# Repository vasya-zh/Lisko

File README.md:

# Lisko

## Overview

Lisko is a EFM32PG23 devboard - micro version of the [Gecko PG23](https://www.silabs.com/development-tools/mcu/32-bit/efm32pg23-pro-kit?tab=overview) development board with NUCLEO-G431KB/Arduino-Nano-v3 pinout.

Lisko is breadboard and custom PCB ready, you can easily check your concept designs with EFM32 MCU

## Features

- EFM32PG23B200F512IM40 MCU with 512kB Flash, 64kB RAM, Secure Vault and almost all reroutable GPIOs
- onboard SWD Flasher based on STM32 with edge USB-C connector
- 32Mbit external Flash chip W25Q32JVSNIQ
- 64Mbit external PSRAM chip APS6404L-SQN-SN
- 24PIN E-INK connector with driver schematics, connected to EFM32PF23 MCU
- External MCU 1.7-3.8V power input for enegry-efficient devices 
- Build in 3.3V LDO with 150mA output pin to power the board from USB or external source VIN pin
- User LED on PA003 pin
- Reset button
- many LEDs for debugging - Power OK, flashing error, Flasher activity
- 30pin Arduino-Nano-v3/NUCLEO-G431KB pinout
- KiCad footprint to use it in your PCBs
- full OSHW, made with KiCad - the best ECAD

## Why did you create this?

We want to help people tinker with beautiful EFM32PG23 microcontroller more cheaply and handily.

## Why EFM32PG23?

This SiLabs MCU has many handy features, we use it mostly because of its Secure Vault and low power consumption for small security devices like crypto wallets or e-locks.

All the chip specs and datasheets can be found on the [EFM32PG23 MCU page](https://www.silabs.com/mcu/32-bit-microcontrollers/efm32pg23-series-2)

## Why do you call it Lisko?

The original SiLabs EFM32 microcontroller line is called Gecko, Lisko is a Finnish word for Gecko, thats simple. 

## How to make Lisko on your own

You can produce Lisko PCBs on any PCB fab you work with, for example, JLCPCB, PCBWAY or OSHPARK, the output files are ready for these fabs.

Gerber files are available in [/production](production/) folder

PCB Specs for order:
- Layers: 4
- Board thickness: 0.8mm - if you make it a different thickness it will not fit inside the USB-C connector
- Surface treatment: ENIG - it's important, don't use HASL or any other surface, it will add thickness and destroy your USB-C cable
- PCB colour/mask: green
- Silkscreen colour: white

You can order PCBs with assembly at your Fab, the [files](production/) are production ready and machine-readable and tested with JLCPCB.

Or order the [parts](docs/) separately and assemble the board on your own.

CSV BOM and interactive HTML BOM are available in [/docs](docs/) folder

All the parts are available at Mouser, Digikey and LCSC (and JLCPCB PCB assembly with LCSC warehouse too)

- [Digikey shared basket](https://www.digikey.fi/short/m47mv8nd)
- [Mouser shared basket](https://www.mouser.fi/ProjectManager/ProjectDetail.aspx?AccessID=fcf13b51e8)

We tried to make BOM as small as possible for this amount of features.

## How to flash your Lisko board

First of all, you need to upload the flasher firmware:

0. Install STM32 DFU flashing software for example [stm32cubeprog](https://www.st.com/en/development-tools/stm32cubeprog.html)
	
	Or install alternative DFU software, for example dfu-util tool:
	
	On a Linux machine you can install it using:

	```
	sudo apt-get install dfu-util
	```
	
	for other systems, see http://dfu-util.sourceforge.net/

1. Hold RESET button and connect Lisko to your PC with a USB-C cable

2. STM32 flasher MCU will go to DFU mode and appear in your system as a DFU device. You can check its availability using:

	```
	dfu-util --list
	```
	You should see something like this:
	```
	dfu-util --list
	dfu-util 0.8

	Copyright 2005-2009 Weston Schmidt, Harald Welte and OpenMoko Inc.
	Copyright 2010-2014 Tormod Volden and Stefan Schmidt
	This program is Free Software and has ABSOLUTELY NO WARRANTY
	Please report bugs to dfu-util@lists.gnumonks.org

	Found DFU: [0483:df11] ver=2200, devnum=49, cfg=1, intf=0, alt=3, name="@Device Feature/0xFFFF0000/01*004 e", serial="315A35663432"
	```

3. Now you can flash the flasher by using:

	```
	dfu-util -a 0 --dfuse-address 0x08000000 -D pilkki_0.0.1.bin
	```

	from the folder, there pilkki_0.0.1.bin file was placed. By default, you can find it in [/flasher-firmware](flasher-firmware/) folder of this repository.

4. Perfect!

If you want to tinker with the flasher firmware, you can find the source code in [Pilkki repo](https://github.com/Kalapaja/pilkki/tree/main/firmware)

## How to program your Lisko board

Binary firmware can be uploaded to Lisko EFM32 MCU using [Pilkki software](https://github.com/Kalapaja/pilkki/tree/main/software)

You can find test projects here:

- In C - in folder [/test-firmware](test-firmware/)

- Or in Rust - [Kampela project](https://github.com/Kalapaja/kampela-firmware)

## How to use Lisko in your PCB project

You can use Lisko with your breadboard prototype, see the pinout diagram and schematics for details.

Or you can integrate Lisko in your PCB as a module with SMD soldering or soldering it with two 15-pin 2.54mm pitch headers.

You can find the KiCad library and 3d models in [/kicad-library](kicad-library/) folder.

An example of module usage can be found in [Kampela Soldering Kit](https://github.com/vasya-zh/kampela-soldering-kit) project.

## About the PCB:

Lisko A1 is made on a 4-layers 0.8mm PCB. 

4 layers make the layout clean and easy and can be produced at any factory with no problem.

Designs and documentation are available in:
- [/kicad](kicad/) - [KiCad](https://www.kicad.org/) design files
- [/docs](docs/) - PDF schematics, interactive HTML BOM, pinout spreadsheet and CSV BOM

0.8mm is used because of the edge USB-C connector used in Lisko to make it cheaper and easier to reproduce. If you can make a device with fewer components, why not do it? Edge USB-C connector inserts directly in a common USB-C cable and works as a USB 2.0 device.

USB Edge connector KiCad library available at [PCB Edge USB connector library](https://github.com/vasya-zh/PCB-Edge-USB-connector-KiCad-library)

## TODO
- Add flasher firmware source code to this repo
- Improve flasher software docs for all OS's and add builds/releases
- Add SWD debugger functions in firmware and Pilkki software/OpenOCD support
- Add the project to https://kitspace.org/

## Contributors

- [Vasilii Zhuravskii](https://github.com/vasya-zh) - Lisko devboard idea, schematics, board design, DFM, docs, tests

- [Yuri Ilin](https://www.youtube.com/@katsuk) - schematics source (Pilkki and Kampela), flasher firmware, EFM32 test firmware in C with E-INK and other features

This project was made at [Alzymologist Oy](https://github.com/alzymologist) as a part of [Kampela](https://kampe.la) project.

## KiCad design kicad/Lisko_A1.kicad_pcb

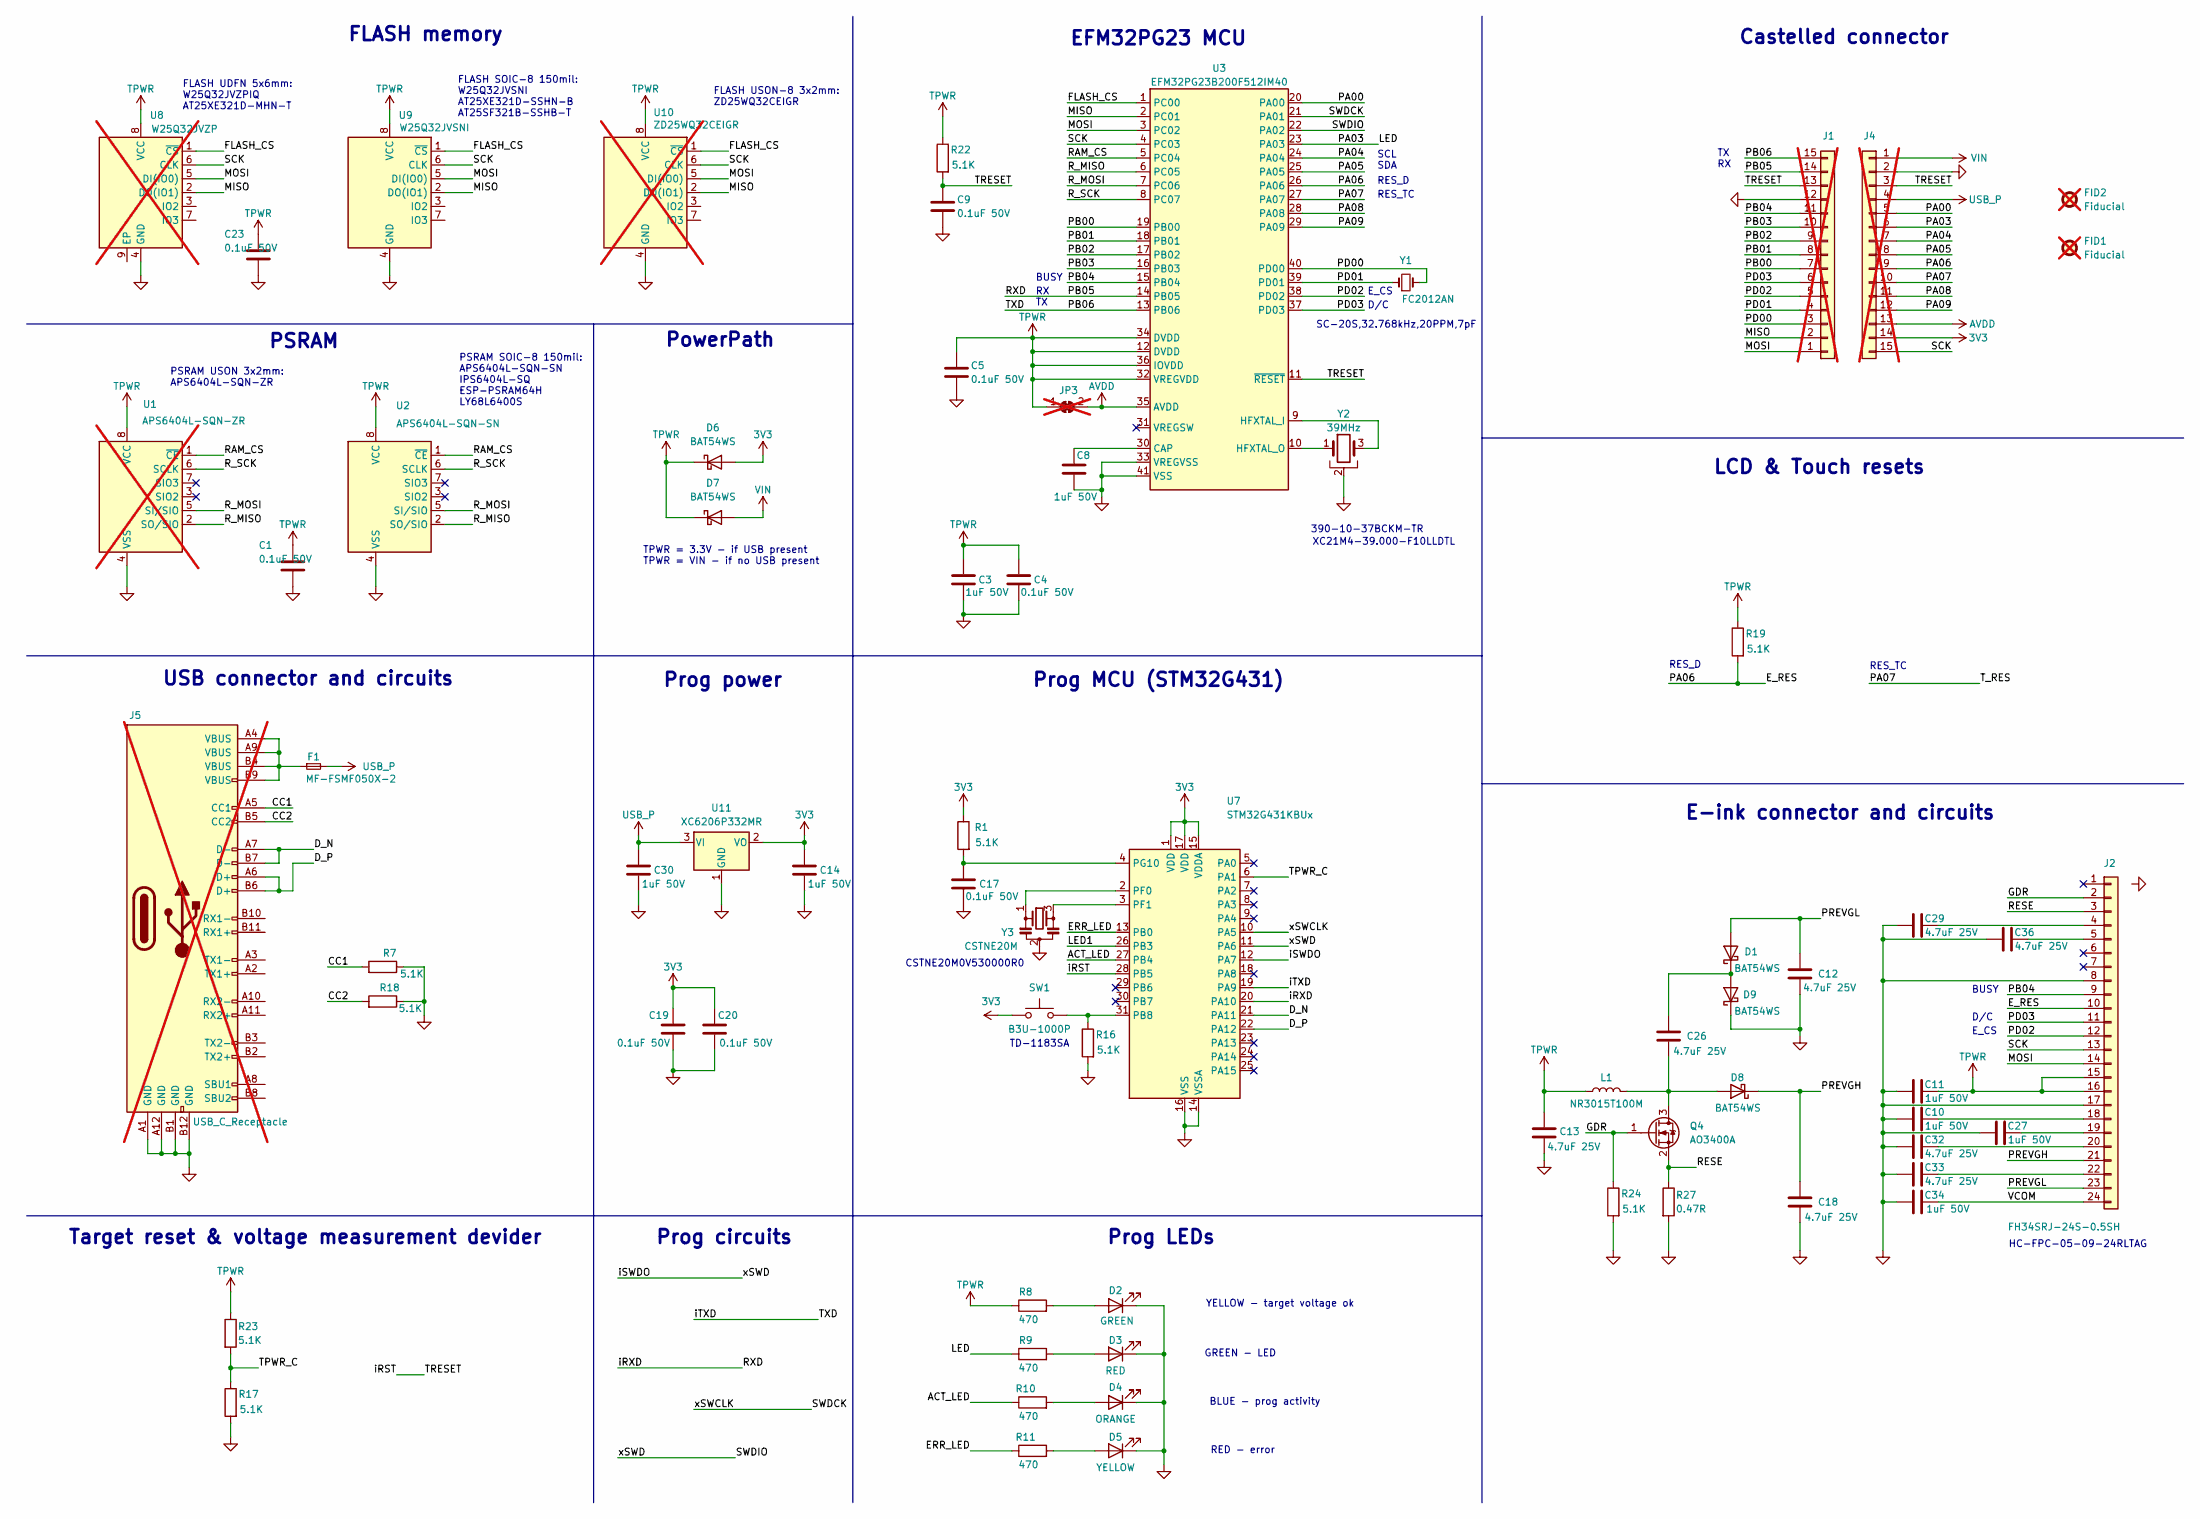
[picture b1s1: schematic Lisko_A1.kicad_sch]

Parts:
C1, C4, C5, C9, C17, C19, C20, C23: 0.1uF 50V; C_0402_1005Metric; Mouser Part # 187-CL05B104KB5NNWC; LCSC Part # C5142567
C3, C8, C10, C11, C14, C27, C30, C34: 1uF 50V; C_0402_1005Metric; Mouser Part # 81-GRM155R61H105KE5J; LCSC Part # C1518208
C12, C13, C18, C26, C29, C32, C33, C36: 4.7uF 25V; C_0603_1608Metric; Mouser Part # 81-GRT188R61E475KE3D; LCSC Part # C20539423
D1, D6, D7, D8, D9: BAT54WS; D_SOD-323F; Mouser Part # 637-BAT54WS; LCSC Part # C3040452
D2: GREEN; LED_0402_1005Metric; Mouser Part # 743-IN-S42BT5G; LCSC Part # C2856703
D3: RED; LED_0402_1005Metric; Mouser Part # 743-IN-S42BTR; LCSC Part # C965790
D4: ORANGE; LED_0402_1005Metric; Mouser Part # 604-APG1005SECT; LCSC Part # C965791
D5: YELLOW; LED_0402_1005Metric; Mouser Part # 743-IN-S42BT5Y; LCSC Part # C965792
F1: MF-FSMF050X-2; Fuse_0603_1608Metric; Mouser Part # MF-FSMF050X-2; LCSC Part # C210357
FID1, FID2: Fiducial; Fiducial_0.5mm_Mask1.5mm; not fitted
J1, J4: Conn_01x15; Connector_Castelled_15pin_2.54mm_withVIA; not fitted
J2: FH34SRJ-24S-0.5SH; Mouser Part # 798-FH34SRJ24S05SH50; LCSC Part # C5213757
J5: USB_C_Receptacle; USB_C_PCB_receptacle_24pin_1mm-cutout; not fitted
JP3: SolderJumper_2_Bridged; SolderJumper-2_P1.3mm_Bridged_Pad1.0x1.5mm; not fitted
L1: NR3015T100M; L_Wuerth_MAPI-3015; Mouser Part # 963-NR3015T100M; LCSC Part # C6364790
Q4: AO3400A; SOT-23; Mouser Part # 78-SI1308EDL-T1-BE3; LCSC Part # C347475
R1, R7, R16, R17, R18, R19, R22, R23, R24: 5.1K; R_0402_1005Metric; Mouser Part # 71-CRCW0402-5.1K-E3; LCSC Part # C2906874
R8, R9, R10, R11: 470; R_0402_1005Metric; Mouser Part # 791-WR04X4700FTL; LCSC Part # C2909361
R27: 0.47R; R_0603_1608Metric; Mouser Part # 603-RL0402FR-070R47L; LCSC Part # C5159706
SW1: B3U-1000P; SW_SPST_B3U-1000P-B; Mouser Part # 653-B3U-1000P-B; LCSC Part # C2905190
U1: APS6404L-SQN-ZR; SON-8-1EP_3x2mm_P0.5mm_EP1.4x1.6mm; not fitted
U2: APS6404L-SQN-SN; SOIC-8_3.9x4.9mm_P1.27mm; Mouser Part # 878-APS6404L-SQN-SN
U3: EFM32PG23B200F512IM40; QFN-40-1EP_5x5mm_P0.4mm_EP3.6x3.6mm; Mouser Part # 634-PG2320F512IM40CR; LCSC Part # C5727544
U7: STM32G431KBUx; QFN-32-1EP_5x5mm_P0.5mm_EP3.45x3.45mm; Mouser Part # 511-STM32G431KBU6; LCSC Part # C1341901
U8: W25Q32JVZP; WSON-8-1EP_6x5mm_P1.27mm_EP3.4x4.3mm; not fitted
U9: W25Q32JVSNI; SOIC-8_3.9x4.9mm_P1.27mm; Mouser Part # 454-W25Q32JVSNIQTR; LCSC Part # C6000506
U10: ZD25WQ32CEIGR; DFN-8-1EP_3x2mm_P0.5mm_EP1.3x1.5mm; not fitted
U11: XC6206P332MR; SOT-23; Mouser Part # 865-XC6206P332MR-G; LCSC Part # C347376
Y1: FC2012AN; Crystal_SMD_2012-2Pin_2.0x1.2mm; Mouser Part # 732-F32768K90NN60KC7; LCSC Part # C97602
Y2: 39MHz; Crystal_SMD_2016-4Pin_2.0x1.6mm; Mouser Part # 520-390-10-37BCKM-TR; LCSC Part # C3034315
Y3: CSTNE20M; Resonator_SMD_Murata_CSTxExxV-3Pin_3.0x1.1mm; Mouser Part # 81-CSTNE20M0V530000R; LCSC Part # C882604

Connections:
3V3: C14.2, C19.1, C20.1, D6.2 (A), J4.14, R1.1, SW1.1, U7.1 (VDD), U7.15 (VDDA), U7.17 (VDD), U11.2 (VO)
/ACT_LED: R10.1, U7.27 (PB4)
/CC1: J5.A5 (CC1), R7.2
/CC2: J5.B5 (CC2), R18.2
/D_N: J5.A7 (D-), J5.B7 (D-), U7.21 (PA11)
/D_P: J5.A6 (D+), J5.B6 (D+), U7.22 (PA12)
/ERR_LED: R11.1, U7.13 (PB0)
/E_RES: J2.10, J4.9, R19.2, U3.26 (PA06)
/FLASH_CS: U3.1 (PC00), U8.1 (~CS), U9.1 (~CS), U10.1 (~CS)
/GDR: J2.2, Q4.1 (G), R24.1
/LED: J4.6, R9.1, U3.23 (PA03)
/LED1: U7.26 (PB3)
/MISO: J1.2, U3.2 (PC01), U8.2 (DO(IO1)), U9.2 (DO(IO1)), U10.2 (DO(IO1))
/MOSI: J1.1, J2.14, U3.3 (PC02), U8.5 (DI(IO0)), U9.5 (DI(IO0)), U10.5 (DI(IO0))
/PA00: J4.5, U3.20 (PA00)
/PA04: J4.7, U3.24 (PA04)
/PA05: J4.8, U3.25 (PA05)
/PA07: J4.10, U3.27 (PA07)
/PA08: J4.11, U3.28 (PA08)
/PA09: J4.12, U3.29 (PA09)
/PB00: J1.7, U3.19 (PB00)
/PB01: J1.8, U3.18 (PB01)
/PB02: J1.9, U3.17 (PB02)
/PB03: J1.10, U3.16 (PB03)
/PB04: J1.11, J2.9, U3.15 (PB04)
/PB05: J1.14, U3.14 (PB05), U7.20 (PA10)
/PB06: J1.15, U3.13 (PB06), U7.19 (PA9)
/PD00: J1.3, U3.40 (PD00), Y1.2
/PD01: J1.4, U3.39 (PD01), Y1.1
/PD02: J1.5, J2.12, U3.38 (PD02)
/PD03: J1.6, J2.11, U3.37 (PD03)
/PREVGH: C18.2, D8.1 (K), J2.21
/PREVGL: C12.2, D1.2 (A), J2.23
/RAM_CS: U1.1 (~CE), U2.1 (~CE), U3.5 (PC04)
/RESE: J2.3, Q4.2 (S), R27.1
/R_MISO: U1.2 (SO/SIO), U2.2 (SO/SIO), U3.6 (PC05)
/R_MOSI: U1.5 (SI/SIO), U2.5 (SI/SIO), U3.7 (PC06)
/R_SCK: U1.6 (SCLK), U2.6 (SCLK), U3.8 (PC07)
/SCK: J2.13, J4.15, U3.4 (PC03), U8.6 (CLK), U9.6 (CLK), U10.6 (CLK)
/SWDCK: U3.21 (PA01), U7.10 (PA5)
/SWDIO: U3.22 (PA02), U7.11 (PA6), U7.12 (PA7)
/TPWR_C: R17.1, R23.2, U7.6 (PA1)
/TRESET: C9.1, J1.13, J4.3, R22.2, U3.11 (~RESET), U7.28 (PB5)
/VCOM: C34.2, J2.24
AVDD: J4.13, JP3.2 (B), U3.35 (AVDD)
GND: C1.2, C3.1, C4.2, C5.2, C8.1, C9.2, C10.1, C11.1, C12.1, C13.1, C14.1, C17.2, C18.1, C19.2, C20.2, C23.2, C27.1, C29.1, C30.1, C32.1, C33.1, C34.1, C36.1, D2.1 (K), D3.1 (K), D4.1 (K), D5.1 (K), D9.1 (K), J1.12, J2.8, J2.17, J4.2, J5.A1 (GND), J5.A12 (GND), J5.B1 (GND), J5.B12 (GND), R7.1, R16.2, R17.2, R18.1, R24.2, R27.2, U1.4 (VSS), U2.4 (VSS), U3.33 (VREGVSS), U3.41 (VSS), U7.14 (VSSA), U7.16 (VSS), U7.32 (VSS), U7.33 (VSS), U8.4 (GND), U9.4 (GND), U10.4 (GND), U11.1 (GND), Y2.2, Y3.2
unnamed: C26.2, D1.1 (K), D9.2 (A)
unnamed: D2.2 (A), R8.2
unnamed: D3.2 (A), R9.2
unnamed: D4.2 (A), R10.2
unnamed: D5.2 (A), R11.2
unnamed: C26.1, D8.2 (A), L1.2, Q4.3 (D)
unnamed: F1.1, J5.A4 (VBUS), J5.A9 (VBUS), J5.B4 (VBUS), J5.B9 (VBUS)
unnamed: C29.2, J2.4
unnamed: C36.2, J2.5
unnamed: C10.2, J2.18
unnamed: C27.2, J2.19
unnamed: C32.2, J2.20
unnamed: C33.2, J2.22
unnamed: C8.2, U3.30 (CAP)
unnamed: U3.9 (HFXTAL_I), Y2.3
unnamed: U3.10 (HFXTAL_O), Y2.1
unnamed: R16.1, SW1.2, U7.31 (PB8)
unnamed: U7.2 (PF0), Y3.1
unnamed: U7.3 (PF1), Y3.3
unnamed: C17.1, R1.2, U7.4 (PG10)
TPWR: C1.1, C3.2, C4.1, C5.1, C11.2, C13.2, C23.1, D6.1 (K), D7.1 (K), J2.15, J2.16, JP3.1 (A), L1.1, R8.1, R19.1, R22.1, R23.1, U1.8 (VCC), U2.8 (VCC), U3.12 (DVDD), U3.32 (VREGVDD), U3.34 (DVDD), U3.36 (IOVDD), U8.8 (VCC), U9.8 (VCC), U10.8 (VCC)
USB_P: C30.2, F1.2, J4.4, U11.3 (VI)
VIN: D7.2 (A), J4.1

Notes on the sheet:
Prog circuits
BUSY
RES_TC
RES_D
USB connector and circuits
RX TX
TX RX
YELLOW - target voltage ok
SC-20S,32.768kHz,20PPM,7pF
RED - error
390-10-37BCKM-TR
Target reset & voltage measurement devider
TD-1183SA
Prog LEDs
BLUE - prog activity
TPWR = 3.3V - if USB present TPWR = VIN - if no USB present
FLASH SOIC-8 150mil: W25Q32JVSNI AT25XE321D-SSHN-B AT25SF321B-SSHB-T
D/C
Prog MCU (STM32G431)
GREEN - LED
PowerPath
FLASH UDFN 5x6mm: W25Q32JVZPIQ AT25XE321D-MHN-T
FLASH memory
FLASH USON-8 3x2mm: ZD25WQ32CEIGR
E_CS
Prog power
SCL SDA
PSRAM
LCD & Touch resets
Castelled connector
HC-FPC-05-09-24RLTAG
EFM32PG23 MCU
E-ink connector and circuits
XC21M4-39.000-F10LLDTL
PSRAM SOIC-8 150mil: APS6404L-SQN-SN IPS6404L-SQ ESP-PSRAM64H LY68L6400S
CSTNE20M0V530000R0
PSRAM USON 3x2mm: APS6404L-SQN-ZR

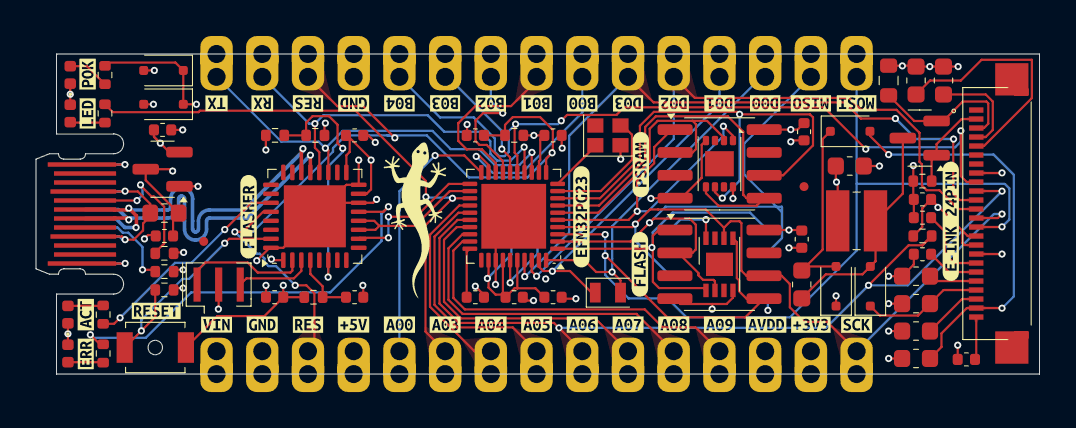
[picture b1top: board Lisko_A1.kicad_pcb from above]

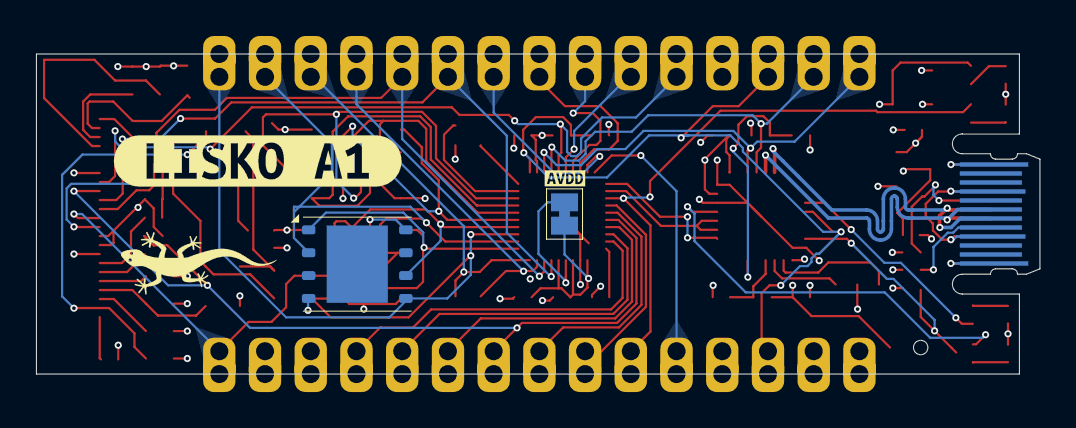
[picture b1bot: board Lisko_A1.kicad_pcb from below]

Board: 4 copper layers, 55.7 x 17.8 mm, 111 parts (4 on the bottom side), 68 nets.

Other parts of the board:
kibuzzard-66363E7A: G***; kibuzzard-66363E7A
kibuzzard-66363E53: G***; kibuzzard-66363E53
kibuzzard-66363EC4: G***; kibuzzard-66363EC4
kibuzzard-66364F8E: G***; kibuzzard-66364F8E
kibuzzard-66369DB4: G***; kibuzzard-66369DB4
kibuzzard-66369E3E: G***; kibuzzard-66369E3E
kibuzzard-663640C7: G***; kibuzzard-663640C7
kibuzzard-663642BF, kibuzzard-663642BF#2: G***; kibuzzard-663642BF
kibuzzard-663642D1, kibuzzard-663642D1#2: G***; kibuzzard-663642D1
kibuzzard-663642E9: G***; kibuzzard-663642E9
kibuzzard-663643C1: G***; kibuzzard-663643C1
kibuzzard-663643D3: G***; kibuzzard-663643D3
kibuzzard-663643E1: G***; kibuzzard-663643E1
kibuzzard-663646E4: G***; kibuzzard-663646E4
kibuzzard-663646FB: G***; kibuzzard-663646FB
kibuzzard-663648A5: G***; kibuzzard-663648A5
kibuzzard-663648B0: G***; kibuzzard-663648B0
kibuzzard-663648B7: G***; kibuzzard-663648B7
kibuzzard-6636429D: G***; kibuzzard-6636429D
kibuzzard-6636433F: G***; kibuzzard-6636433F
kibuzzard-6636439B: G***; kibuzzard-6636439B
kibuzzard-6636478B: G***; kibuzzard-6636478B
kibuzzard-66364172: G***; kibuzzard-66364172
kibuzzard-66364309: G***; kibuzzard-66364309
kibuzzard-66364333: G***; kibuzzard-66364333
kibuzzard-66364349: G***; kibuzzard-66364349
kibuzzard-66364382: G***; kibuzzard-66364382
kibuzzard-66364387: G***; kibuzzard-66364387
kibuzzard-66364390: G***; kibuzzard-66364390
kibuzzard-66364428: G***; kibuzzard-66364428
kibuzzard-66364435: G***; kibuzzard-66364435
kibuzzard-66364443: G***; kibuzzard-66364443
kibuzzard-66364453: G***; kibuzzard-66364453
kibuzzard-66364637: G***; kibuzzard-66364637
kibuzzard-66364709: G***; kibuzzard-66364709
kibuzzard-66364715: G***; kibuzzard-66364715
kibuzzard-66364725: G***; kibuzzard-66364725
kibuzzard-66364732: G***; kibuzzard-66364732
kibuzzard-66364791: G***; kibuzzard-66364791
kibuzzard-66364895: G***; kibuzzard-66364895

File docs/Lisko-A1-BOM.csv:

"Reference","Part Number","Value","Qty","Footprint","DNP","LCSC Part #","Mouser Part #"
"C1,C4,C5,C9,C17,C19,C20,C23","CL05B104KB5NNWC","0.1uF 50V","8","Capacitor_SMD:C_0402_1005Metric","","C5142567","187-CL05B104KB5NNWC"
"C3,C8,C10,C11,C14,C27,C30,C34","GRM155R61H105KE5J","1uF 50V","8","Capacitor_SMD:C_0402_1005Metric","","C1518208","81-GRM155R61H105KE5J"
"C12,C13,C18,C26,C29,C32,C33,C36","GRT188R61E475KE3D","4.7uF 25V","8","Capacitor_SMD:C_0603_1608Metric","","C20539423","81-GRT188R61E475KE3D"
"D1,D6,D7,D8,D9","BAT54WS","BAT54WS","5","Diode_SMD:D_SOD-323F","","C3040452","637-BAT54WS"
"D2","IN-S42BT5G","GREEN","1","LED_SMD:LED_0402_1005Metric","","C2856703","743-IN-S42BT5G"
"D3","IN-S42BTR","RED","1","LED_SMD:LED_0402_1005Metric","","C965790","743-IN-S42BTR"
"D4","APG1005SECT","ORANGE","1","LED_SMD:LED_0402_1005Metric","","C965791","604-APG1005SECT"
"D5","IN-S42BT5Y","YELLOW","1","LED_SMD:LED_0402_1005Metric","","C965792","743-IN-S42BT5Y"
"F1","MF-FSMF050X-2","MF-FSMF050X-2","1","Fuse:Fuse_0603_1608Metric","","C210357","MF-FSMF050X-2"
"J2","FH34SRJ24S05SH50","FH34SRJ-24S-0.5SH","1","Kampela_components:FH34SRJ-24S-0.5SH","","C5213757","798-FH34SRJ24S05SH50"
"L1","NR3015T100M","NR3015T100M","1","Inductor_SMD:L_Wuerth_MAPI-3015","","C6364790","963-NR3015T100M"
"Q4","SI1308EDL-T1-BE3","AO3400A","1","Package_TO_SOT_SMD:SOT-23","","C347475","78-SI1308EDL-T1-BE3"
"R1,R7,R16,R17,R18,R19,R22,R23,R24","CRCW0402-5.1K-E3","5.1K","9","Resistor_SMD:R_0402_1005Metric","","C2906874","71-CRCW0402-5.1K-E3"
"R8,R9,R10,R11","WR04X4700FTL","470","4","Resistor_SMD:R_0402_1005Metric","","C2909361","791-WR04X4700FTL"
"R27","RL0402FR-070R47L","0.47R","1","Resistor_SMD:R_0603_1608Metric","","C5159706","603-RL0402FR-070R47L"
"SW1","B3U-1000P-B","B3U-1000P","1","Button_Switch_SMD:SW_SPST_B3U-1000P-B","","C2905190","653-B3U-1000P-B"
"U2","APS6404L-SQN-SN","APS6404L-SQN-SN","1","Package_SO:SOIC-8_3.9x4.9mm_P1.27mm","","-","878-APS6404L-SQN-SN"
"U3","EFM32PG23B200F512IM40","EFM32PG23B200F512IM40","1","Package_DFN_QFN:QFN-40-1EP_5x5mm_P0.4mm_EP3.6x3.6mm","","C5727544","634-PG2320F512IM40CR"
"U7","STM32G431KBU6","STM32G431KBUx","1","Package_DFN_QFN:QFN-32-1EP_5x5mm_P0.5mm_EP3.45x3.45mm","","C1341901","511-STM32G431KBU6"
"U9","W25Q32JVSNIQTR","W25Q32JVSNI","1","Package_SO:SOIC-8_3.9x4.9mm_P1.27mm","","C6000506","454-W25Q32JVSNIQTR"
"U11","XC6206P332MR","XC6206P332MR","1","Package_TO_SOT_SMD:SOT-23","","C347376","865-XC6206P332MR-G"
"Y1","F32768K90NN60KC7","FC2012AN","1","Kampela_components:Crystal_SMD_2012-2Pin_2.0x1.2mm","","C97602","732-F32768K90NN60KC7"
"Y2","390-10-37BCKM-TR","39MHz","1","Kampela_components:Crystal_SMD_2016-4Pin_2.0x1.6mm","","C3034315","520-390-10-37BCKM-TR"
"Y3","CSTNE20M0V530000R","CSTNE20M","1","Crystal:Resonator_SMD_Murata_CSTxExxV-3Pin_3.0x1.1mm","","C882604","81-CSTNE20M0V530000R"

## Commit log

2024-05-14 A1 initial commit
2024-05-14 A1 initial commit (#1)
